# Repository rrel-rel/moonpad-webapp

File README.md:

# moonpad-webapp
Webapp for adjusting moonpad settings

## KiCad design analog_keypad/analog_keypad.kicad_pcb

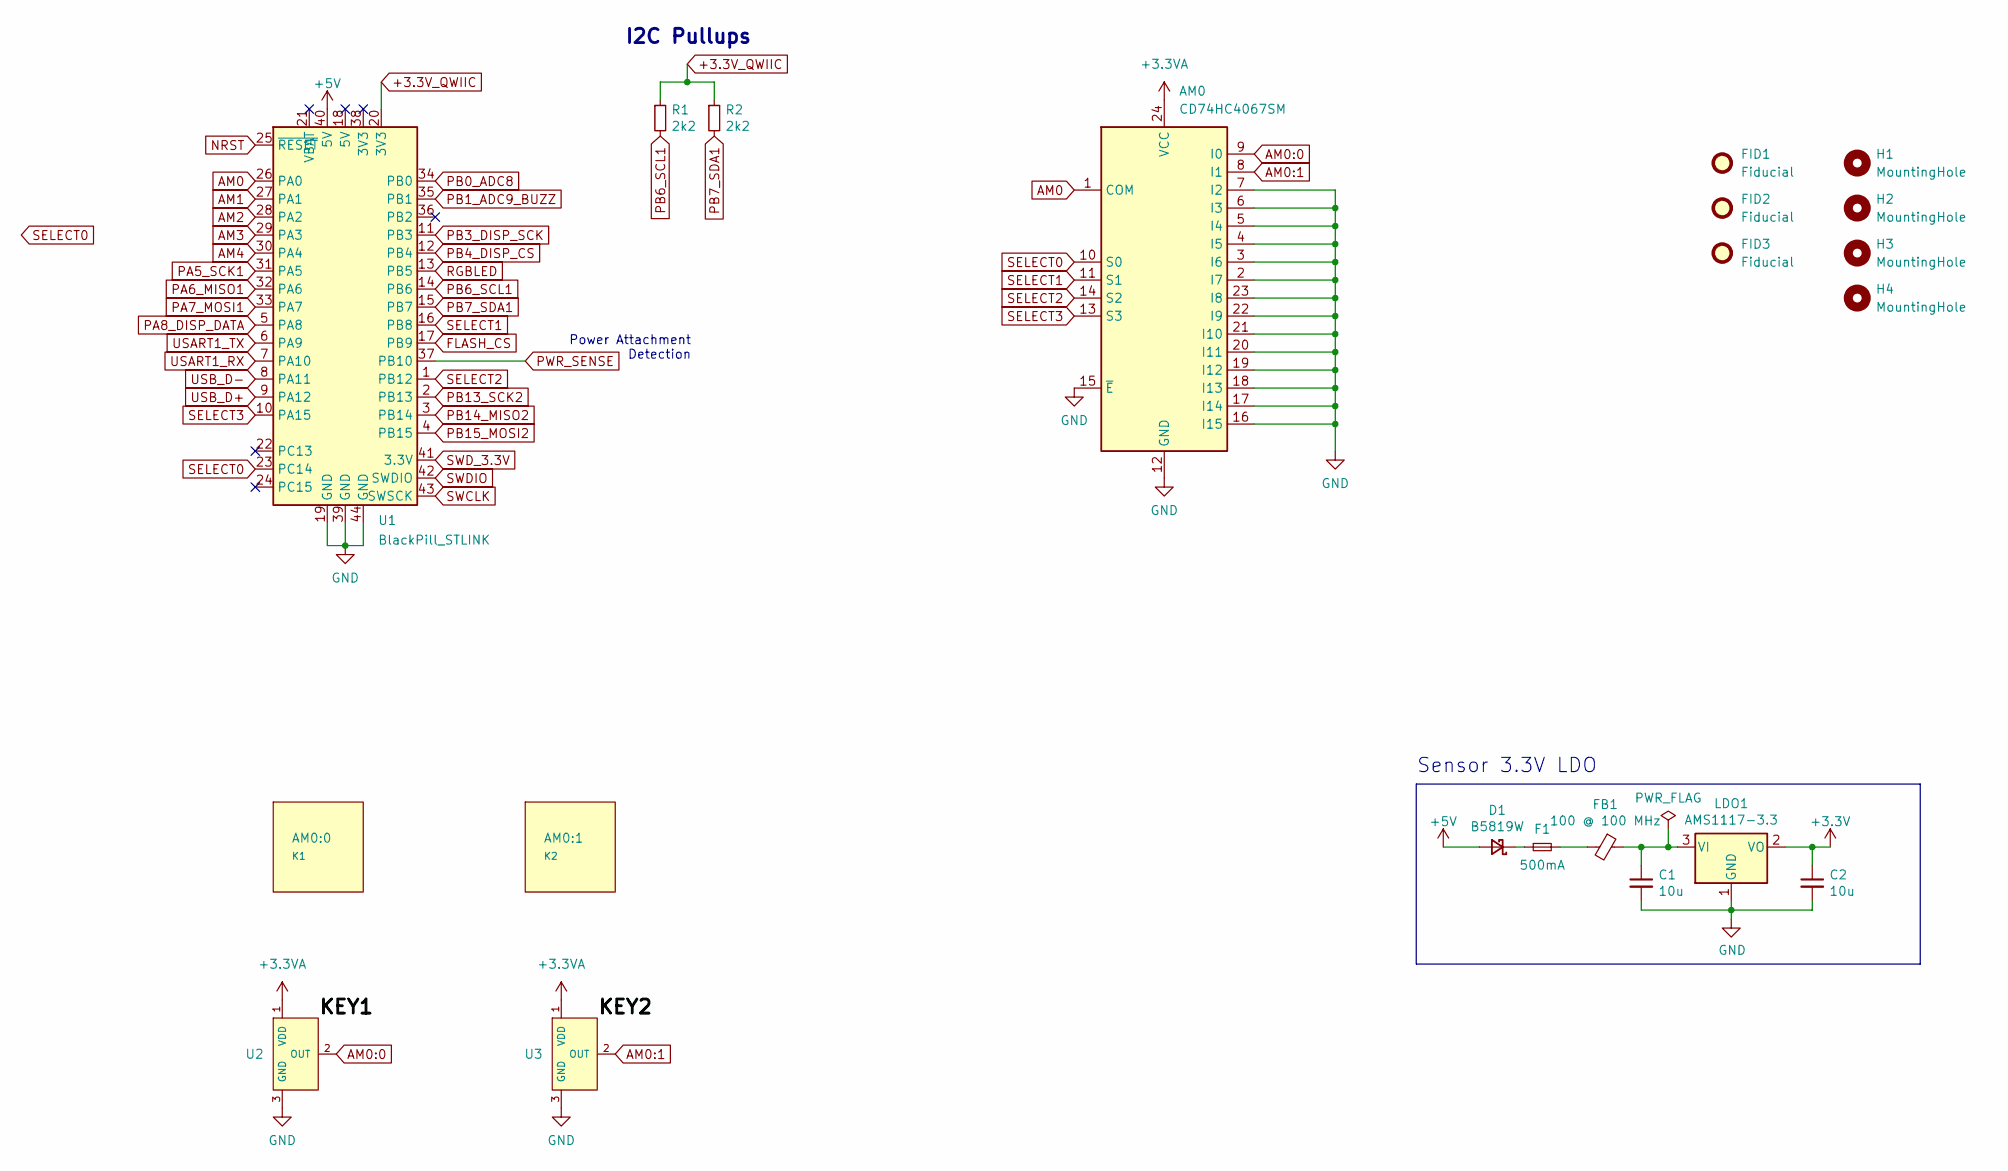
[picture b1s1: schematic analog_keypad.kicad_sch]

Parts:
AM0: CD74HC4067SM; SSOP-24_5.3x8.2mm_P0.65mm
AM0:0: K1; VoidSwitch_1u_SMD
AM0:1: K2; VoidSwitch_1u_SMD
C1, C2: 10u; C_0402_1005Metric; MPN CL05A106MQ5NUNC; LCSC Part C15525
D1: B5819W; D_SOD-123; MPN B5819W; LCSC Part C8598
F1: 500mA; Fuse_0603_1608Metric; LCSC Part C261937
FB1: 100 @ 100 MHz; L_0805_2012Metric; MPN GZ2012D101TF; LCSC Part C1015
FID1, FID2, FID3: Fiducial; Fiducial_1mm_Mask2mm
H1, H2, H3, H4: MountingHole; MountingHole_3.2mm_M3_DIN965_Pad
LDO1: AMS1117-3.3; SOT-223-3_TabPin2; MPN AMS1117-3.3; LCSC Part C6186
R1, R2: 2k2; R_0402_1005Metric; MPN 0402WGF2201TCE; LCSC Part C25879
U1: BlackPill_STLINK
U2, U3: Hall_Sensor; SOT-23; MPN GH39FKSW; LCSC Part C266230

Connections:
+3.3VA: AM0.24 (VCC), U2.1 (VDD), U3.1 (VDD)
+3.3V_QWIIC: R1.1, R2.1, U1.20 (3V3); also elsewhere on the board
+3V3: C2.1, LDO1.2 (VO)
+5V: D1.2 (A), U1.40 (5V); also elsewhere on the board
AM0: AM0.1 (COM), U1.26 (PA0); also elsewhere on the board
AM0:0: AM0.9 (I0), U2.2 (OUT)
AM0:1: AM0.8 (I1), U3.2 (OUT)
AM1: U1.27 (PA1); also elsewhere on the board
AM2: U1.28 (PA2); also elsewhere on the board
AM3: U1.29 (PA3); also elsewhere on the board
AM4: U1.30 (PA4); also elsewhere on the board
FLASH_CS: U1.17 (PB9); also elsewhere on the board
GND: AM0.2 (I7), AM0.3 (I6), AM0.4 (I5), AM0.5 (I4), AM0.6 (I3), AM0.7 (I2), AM0.12 (GND), AM0.15 (~E), AM0.16 (I15), AM0.17 (I14), AM0.18 (I13), AM0.19 (I12), AM0.20 (I11), AM0.21 (I10), AM0.22 (I9), AM0.23 (I8), C1.2, C2.2, LDO1.1 (GND), U1.19 (GND), U1.39 (GND), U1.44 (GND), U2.3 (GND), U3.3 (GND); also elsewhere on the board
NRST: U1.25 (~RESET); also elsewhere on the board
unnamed: C1.1, FB1.1, LDO1.3 (VI)
unnamed: D1.1 (K), F1.1
unnamed: F1.2, FB1.2
PA5_SCK1: U1.31 (PA5); also elsewhere on the board
PA6_MISO1: U1.32 (PA6); also elsewhere on the board
PA7_MOSI1: U1.33 (PA7); also elsewhere on the board
PA8_DISP_DATA: U1.5 (PA8); also elsewhere on the board
PB0_ADC8: U1.34 (PB0); also elsewhere on the board
PB1_ADC9_BUZZ: U1.35 (PB1); also elsewhere on the board
PB3_DISP_SCK: U1.11 (PB3); also elsewhere on the board
PB4_DISP_CS: U1.12 (PB4); also elsewhere on the board
PB6_SCL1: R1.2, U1.14 (PB6); also elsewhere on the board
PB7_SDA1: R2.2, U1.15 (PB7); also elsewhere on the board
PB13_SCK2: U1.2 (PB13); also elsewhere on the board
PB14_MISO2: U1.3 (PB14); also elsewhere on the board
PB15_MOSI2: U1.4 (PB15); also elsewhere on the board
PWR_SENSE: U1.37 (PB10); also elsewhere on the board
RGBLED: U1.13 (PB5); also elsewhere on the board
SELECT0: AM0.10 (S0), U1.23 (PC14); also elsewhere on the board
SELECT1: AM0.11 (S1), U1.16 (PB8); also elsewhere on the board
SELECT2: AM0.14 (S2), U1.1 (PB12); also elsewhere on the board
SELECT3: AM0.13 (S3), U1.10 (PA15); also elsewhere on the board
SWCLK: U1.43 (SWSCK); also elsewhere on the board
SWDIO: U1.42 (SWDIO); also elsewhere on the board
SWD_3.3V: U1.41 (3.3V); also elsewhere on the board
USART1_RX: U1.7 (PA10); also elsewhere on the board
USART1_TX: U1.6 (PA9); also elsewhere on the board
USB_D+: U1.9 (PA12); also elsewhere on the board
USB_D-: U1.8 (PA11); also elsewhere on the board

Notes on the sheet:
Sensor 3.3V LDO
Power Attachment Detection
I2C Pullups

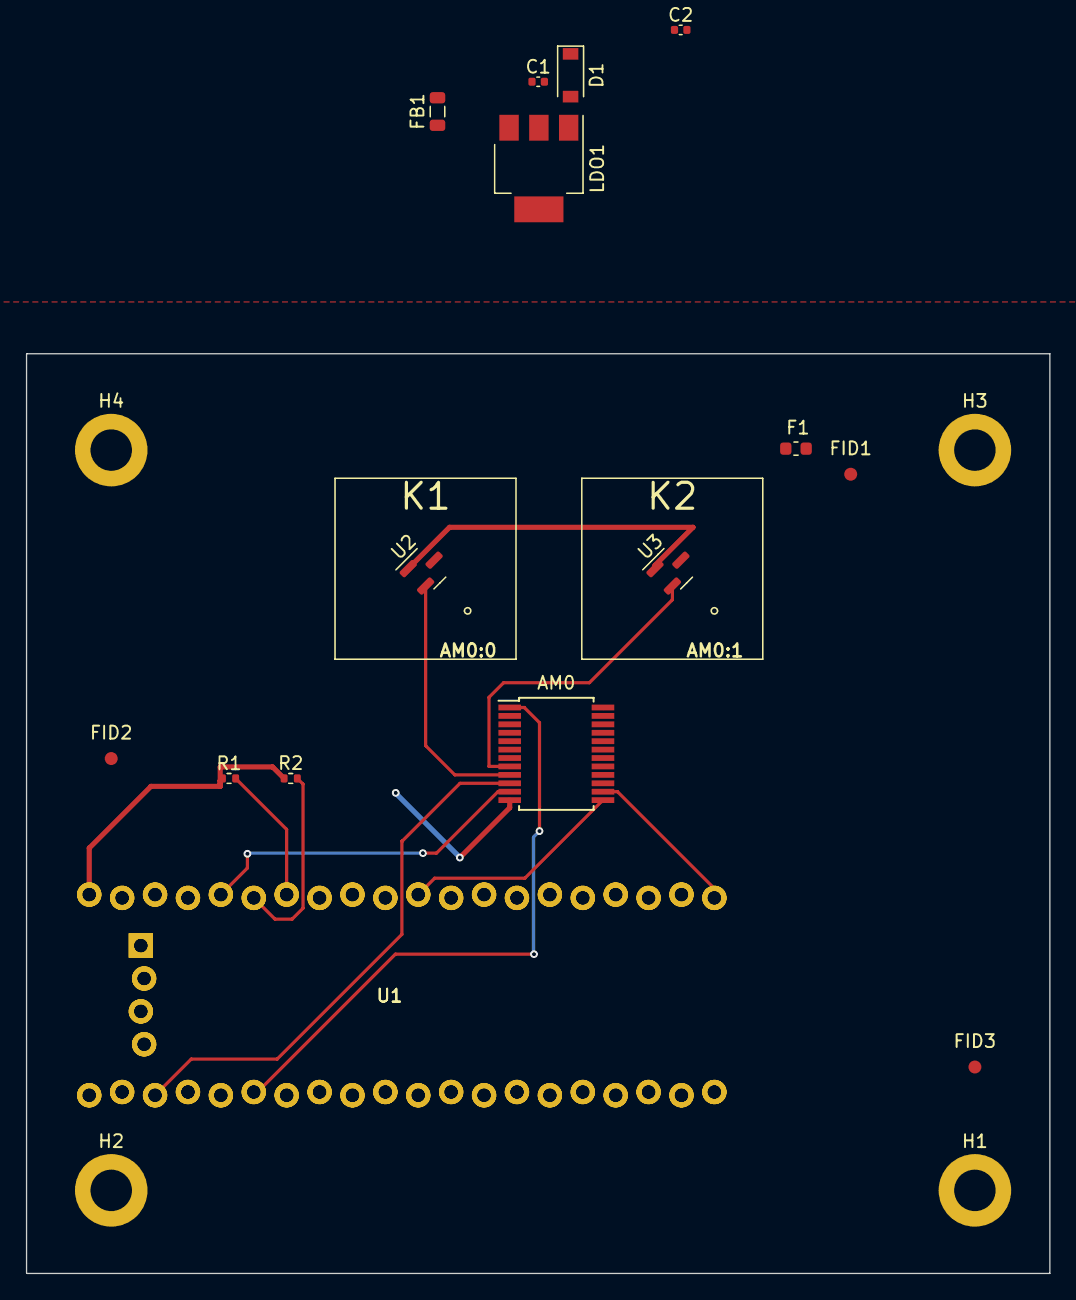
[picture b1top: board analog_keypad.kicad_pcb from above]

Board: 2 copper layers, 79.0 x 71.0 mm, 22 parts (0 on the bottom side), 43 nets.

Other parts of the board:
U1#2: BlackPill_STLINK

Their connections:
+3.3V_QWIIC: U1#2.20 (3V3); also elsewhere on the board
+5V: U1#2.40 (5V); also elsewhere on the board
AM0: U1#2.26 (PA0); also elsewhere on the board
AM1: U1#2.27 (PA1); also elsewhere on the board
AM2: U1#2.28 (PA2); also elsewhere on the board
AM3: U1#2.29 (PA3); also elsewhere on the board
AM4: U1#2.30 (PA4); also elsewhere on the board
FLASH_CS: U1#2.17 (PB9); also elsewhere on the board
GND: U1#2.19 (GND), U1#2.39 (GND), U1#2.44 (GND); also elsewhere on the board
NRST: U1#2.25 (~RESET); also elsewhere on the board
PA5_SCK1: U1#2.31 (PA5); also elsewhere on the board
PA6_MISO1: U1#2.32 (PA6); also elsewhere on the board
PA7_MOSI1: U1#2.33 (PA7); also elsewhere on the board
PA8_DISP_DATA: U1#2.5 (PA8); also elsewhere on the board
PB0_ADC8: U1#2.34 (PB0); also elsewhere on the board
PB1_ADC9_BUZZ: U1#2.35 (PB1); also elsewhere on the board
PB3_DISP_SCK: U1#2.11 (PB3); also elsewhere on the board
PB4_DISP_CS: U1#2.12 (PB4); also elsewhere on the board
PB6_SCL1: U1#2.14 (PB6); also elsewhere on the board
PB7_SDA1: U1#2.15 (PB7); also elsewhere on the board
PB13_SCK2: U1#2.2 (PB13); also elsewhere on the board
PB14_MISO2: U1#2.3 (PB14); also elsewhere on the board
PB15_MOSI2: U1#2.4 (PB15); also elsewhere on the board
PWR_SENSE: U1#2.37 (PB10); also elsewhere on the board
RGBLED: U1#2.13 (PB5); also elsewhere on the board
SELECT0: U1#2.23 (PC14); also elsewhere on the board
SELECT1: U1#2.16 (PB8); also elsewhere on the board
SELECT2: U1#2.1 (PB12); also elsewhere on the board
SELECT3: U1#2.10 (PA15); also elsewhere on the board
SWCLK: U1#2.43 (SWSCK); also elsewhere on the board
SWDIO: U1#2.42 (SWDIO); also elsewhere on the board
SWD_3.3V: U1#2.41 (3.3V); also elsewhere on the board
USART1_RX: U1#2.7 (PA10); also elsewhere on the board
USART1_TX: U1#2.6 (PA9); also elsewhere on the board
USB_D+: U1#2.9 (PA12); also elsewhere on the board
USB_D-: U1#2.8 (PA11); also elsewhere on the board
